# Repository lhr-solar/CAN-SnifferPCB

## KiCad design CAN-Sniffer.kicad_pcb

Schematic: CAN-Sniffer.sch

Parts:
C1, C6: 10 uF; C_0805_2012Metric
C2, C3, C7: 0.1 uF; C_0805_2012Metric
C4, C8: 0.01 uF; C_0805_2012Metric
C5: 0.22 uF; C_0805_2012Metric
H1, H2, H3, H4: MountingHole; MountingHole_3mm
J1: CANConnIn; Molex_MicroFit3.0_1x4xP3.00mm_PolarizingPeg_Vertical
J2: CANConnOut; Molex_MicroFit3.0_1x4xP3.00mm_PolarizingPeg_Vertical
JP1: Jumper_NC_Small; PinHeader_1x02_P2.54mm_Vertical
L1, L2: 2 kH; L_0805_2012Metric
LOGO1: UTSVT Logo; UTSVT_Logo_Symbol
LOGO2: Dr Hallock; Hallock_Image_Small
R1: 0; R_0805_2012Metric
R2, R3: 60; R_0805_2012Metric
TP1, TP2, TP3, TP4: TestPoint; TestPoint_Keystone_5005-5009_Compact
U1: Nucleo_L432KC; NucleoL432KC
U2: ADM3055E; SOIC-20W_7.5x15.4mm_Pitch1.27mm
U3: CDSOT23-T24CAN; SOT-23W

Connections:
+3V3: C3.1, C4.1, U1.17, U2.4
+5V: C1.1, C2.1, U1.27, U2.3
/CAN_H: J1.3, J2.3, R2.2, TP3.1, U2.14, U3.1
/CAN_L: J1.4, J2.4, R3.2, TP4.1, U2.13, U3.2
/CAN_Rx: TP2.1, U1.13, U2.5
/CAN_Tx: TP1.1, U1.5, U2.7
/RSlope: R1.2, U2.12
GND: C1.2, C2.2, C3.2, C4.2, U1.4, U1.29, U2.1, U2.2, U2.10
unnamed: C5.1, L1.2, U2.19
unnamed: C5.2, L2.2, U2.18, U2.20
unnamed: C6.1, C7.1, C8.1, J1.1, J2.1, L1.1, U2.16
unnamed: C6.2, C7.2, C8.2, J1.2, J2.2, L2.1, R1.1, U2.11, U2.15, U3.3
unnamed: JP1.1, R2.1
unnamed: JP1.2, R3.1

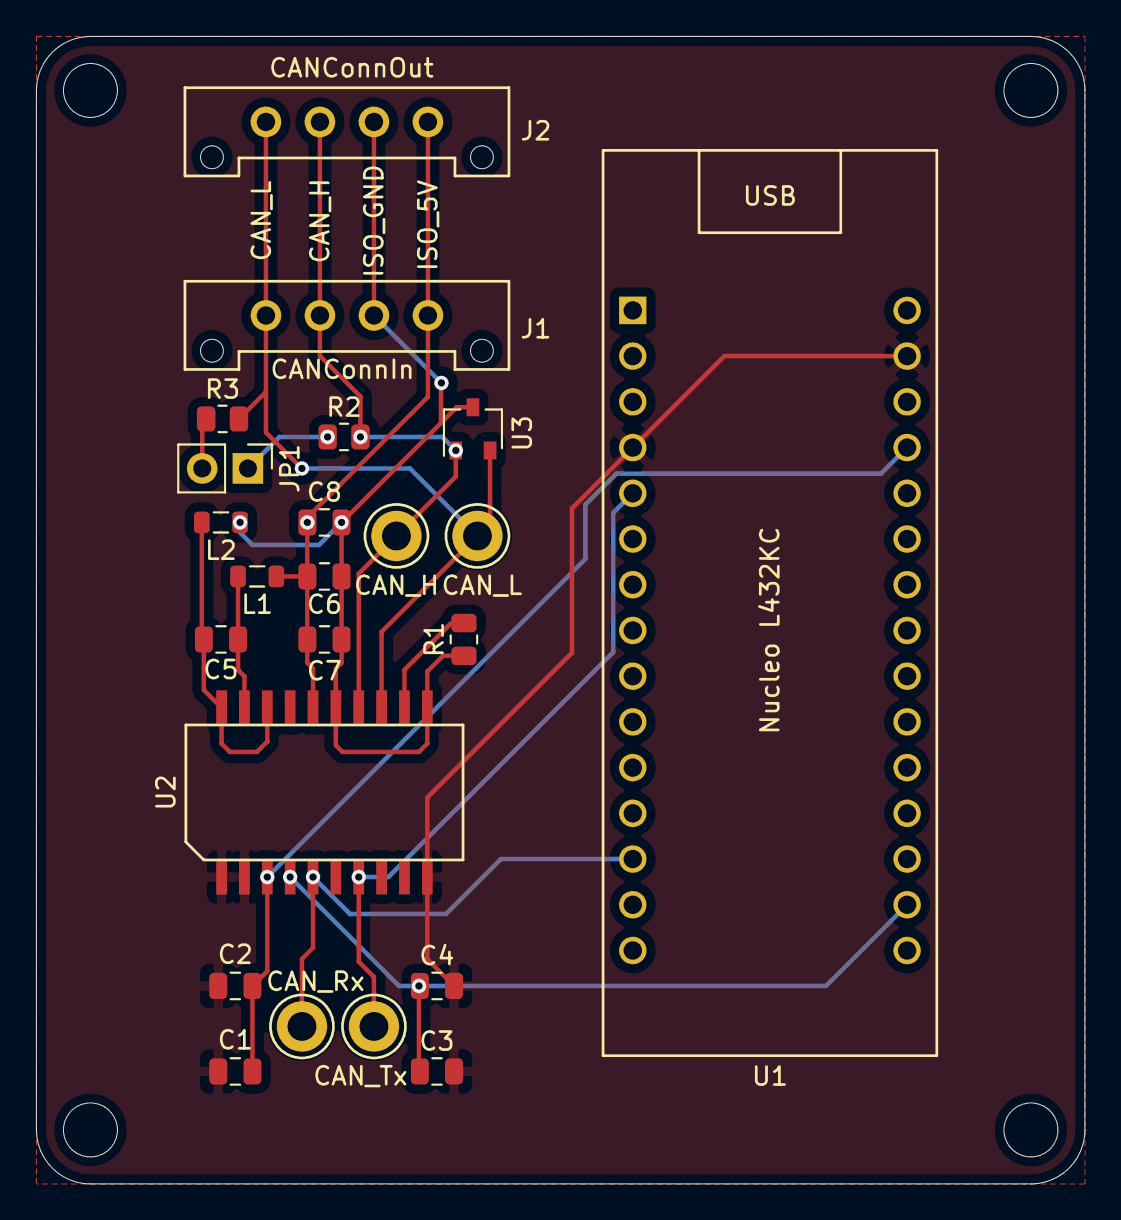
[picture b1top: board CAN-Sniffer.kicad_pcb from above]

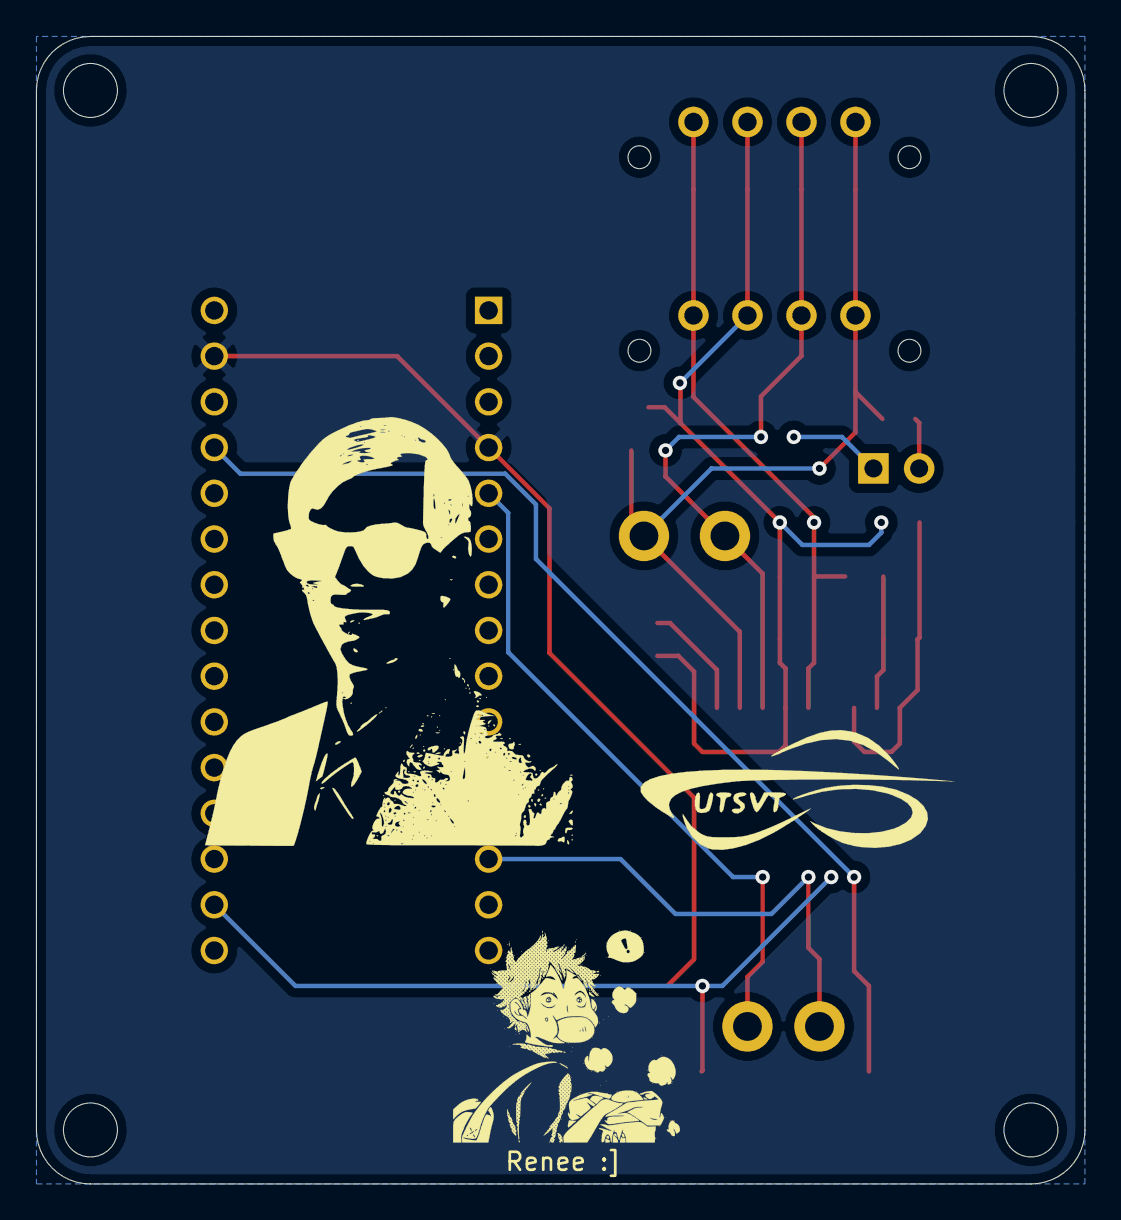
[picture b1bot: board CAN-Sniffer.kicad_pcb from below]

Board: 2 copper layers, 58.2 x 63.8 mm, 29 parts (2 on the bottom side), 14 nets.

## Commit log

2020-08-15 Formats kicad project
2020-08-15 Deletes common folder
2020-08-15 Adds common library submodule
2020-08-15 Adds documentation files
2020-08-15 Adds Terminating resistor label
2020-09-01 Renames project to not include PCB
2020-10-03 Adds QuAC
2021-10-30 Rearranged PCB Layout for CAN Sniffer
